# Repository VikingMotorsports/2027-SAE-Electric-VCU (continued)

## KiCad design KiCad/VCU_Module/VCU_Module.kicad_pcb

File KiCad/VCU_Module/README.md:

---
title: "**Viking MotorSports VCU Module**"
subtitle: |
  **Fabrication and Assembly Information**\
  For build TIME-STAMP
fontsize: 10pt
geometry:
  - margin=0.5in
toc: true
toc-depth: 2
colorlinks: true
urlcolor: blue
---

\newpage

# About this Board

## Board Description

*Describe board here*

## Documentation Links

*Link to documentation here*

## Documentation Files

| Filename                        | Notes                                    |
| ------------------------------- | ---------------------------------------- |
| README.pdf                      | This README file                         |
| PROJECT-NAME-outline.dxf        | Board outline (with holes) in DXF format |
| PROJECT-NAME-pcba.step          | 3D model of PCBA (with components)       |
| PROJECT-NAME-render-bot.jpg     | Render of the top of the 3D model        |
| PROJECT-NAME-render-bot.jpg     | Render of the bottom of the 3D model     |
| PROJECT-NAME-schematic.pdf      | PDF of board schematics                  |

## Contact Information

- Website: *website*
- Email: *email*

## Board Renders

{width=50%}
{width=50%}

\newpage

# Printed Circuit Board (PCB) Fabrication Information

## Board Info

- 2 layer board
- Bounding box is *TBD*
- Board thickness is 1.59 mm (0.063 inch)

## Board Requirements

- Design Rules
    - Minimum Trace / Space design rulea: 0.1524 mm (6.0 mil) / 0.1524 mm (6.0 mil)
    - Outer dimension router tolerance: +/- 0.254 mm (10.0 mil)
    - Hole placement tolerance: +/- 0.075 mm (3.0 mil)
- Drills
   - Drill Positional Tolerance: 0.051 mm (2.0 mil)
   - Drill Size tolerance: +/- 0.064 mm (2.5 mil)
- Plated/Un-plated holes
  - There are no un-plated (NPT) holes
  - There are 96 plated through (PTH) holes
  - PTH minimum diameter: 0.254 mm (10 mil)
  - PTH minimum annulus: 0.102 mm (4 mil) radius
- Outline/Routing
  - No requirements.
- Slots
  - There are no slots.
- Cutouts
  - There are no cutouts
- There are 3 fiducials on the top layer.
- Panel tabs ("mouse bites")
   - Card edges must be smooth; no mouse bites or other intrusions into the card outline.
   - If external mouse bites are required, minimize and customer will remove by hand before assembly.
- If not otherwise specified, build to IPC 6012 Class 2 or better.

## Materials

- No requirements for materials.
- Copper Surface treatment should be ENIG, althogh immersion Silver is acceptable.
- White silkscreen on top and bottom surface
- Taiyo PSR-4000 or equivalent soldermask on top and bottom, no requirements for color.

## Stack Up

- Any FR4 like material is acceptable.
- 1 oz Copper on top and bottom layers
- 1.6 mm thick when done (1/16 inch)

## Array / Panel Information

- Coordinate with Contract Manufacturer (CM) for optimal size of this panel.
- If no feedback from CM, then produce single boards (no panel).

## Fabrication Files

### IPC-2581 File

| Filename                 | Notes                                   |
| ------------------------ | --------------------------------------- |
| PROJECT-NAME-ipc2581.xml | IPC-2581 board information file         |

### Legacy PCB Files

| Filename                      | Notes                                         |
| ------------------------------| --------------------------------------------- |
| PROJECT-NAME-Edge_Cuts.gbr    | RS274X file for the dimension (outline) layer |
| PROJECT-NAME-F_Silkscreen.gbr | RS274X file for the top silkscreen            |
| PROJECT-NAME-F_Mask.gbr       | RS274X file for the top soldermask            |
| PROJECT-NAME-F_Cu.gbr         | RS274X file for the top copper layer          |
| PROJECT-NAME-In1_Cu.gbr       | RS274X file for the layer 2 copper            |
| PROJECT-NAME-In2_Cu.gbr       | RS274X file for the layer 3 copper            |
| PROJECT-NAME-B_Cu.gbr         | RS274X file for the bottom copper layer       |
| PROJECT-NAME-B_Mask.gbr       | RS274X file for the bottom soldermask         |
| PROJECT-NAME-B_Silkscreen.gbr | RS274X file for the bottom silkscreen         |
| PROJECT-NAME-NPTH.drl         | Excellon file for non-plated through holes    |
| PROJECT-NAME-PTH.drl          | Excellon file for plated through holes        | 

\newpage

# Printed Circuit Board Assembly (PCBA) Information

## Assembly Info

- All components are on the top side of the board.
- This PCBA has two components that are SMT components with through-hole mechanical leads.

## Assembly Requirements

- Assemble to IPC Class 2 or better
- Solder paste can be ROHS or leaded.
- No clean, or Aqueous flux and wash, can be used.
- No conformal coating.

## Component Specific Assembly Information

- None

## Assembly Files

### IPC-2581 File

| Filename                 | Notes                           |
| ------------------------ | ------------------------------- |
| PROJECT-NAME-ipc2581.xml | IPC-2581 board information file |

### Bill of Materials (BOM)

| Filename             | Description                            |
| -------------------- | -------------------------------------- |
| PROJECT-NAME-bom.csv | BOM in Comma Separated Variable format |

### Solder Paste Stencils

| Filename                 | Notes                                            |
| ------------------------ | ------------------------------------------------ |
| PROJECT-NAME-B_Paste.gbr | RS274X file for top/front solder paste stencil   |
| PROJECT-NAME-F_Paste.gbr | RS274X file for bottom/back solder paste stencil |

### Mounting/Placement Location

| Filename            | Description                                 |
| ------------------- | ------------------------------------------- |
| PROJECT-NAME-3u.pos | Pick and place locations for components     |

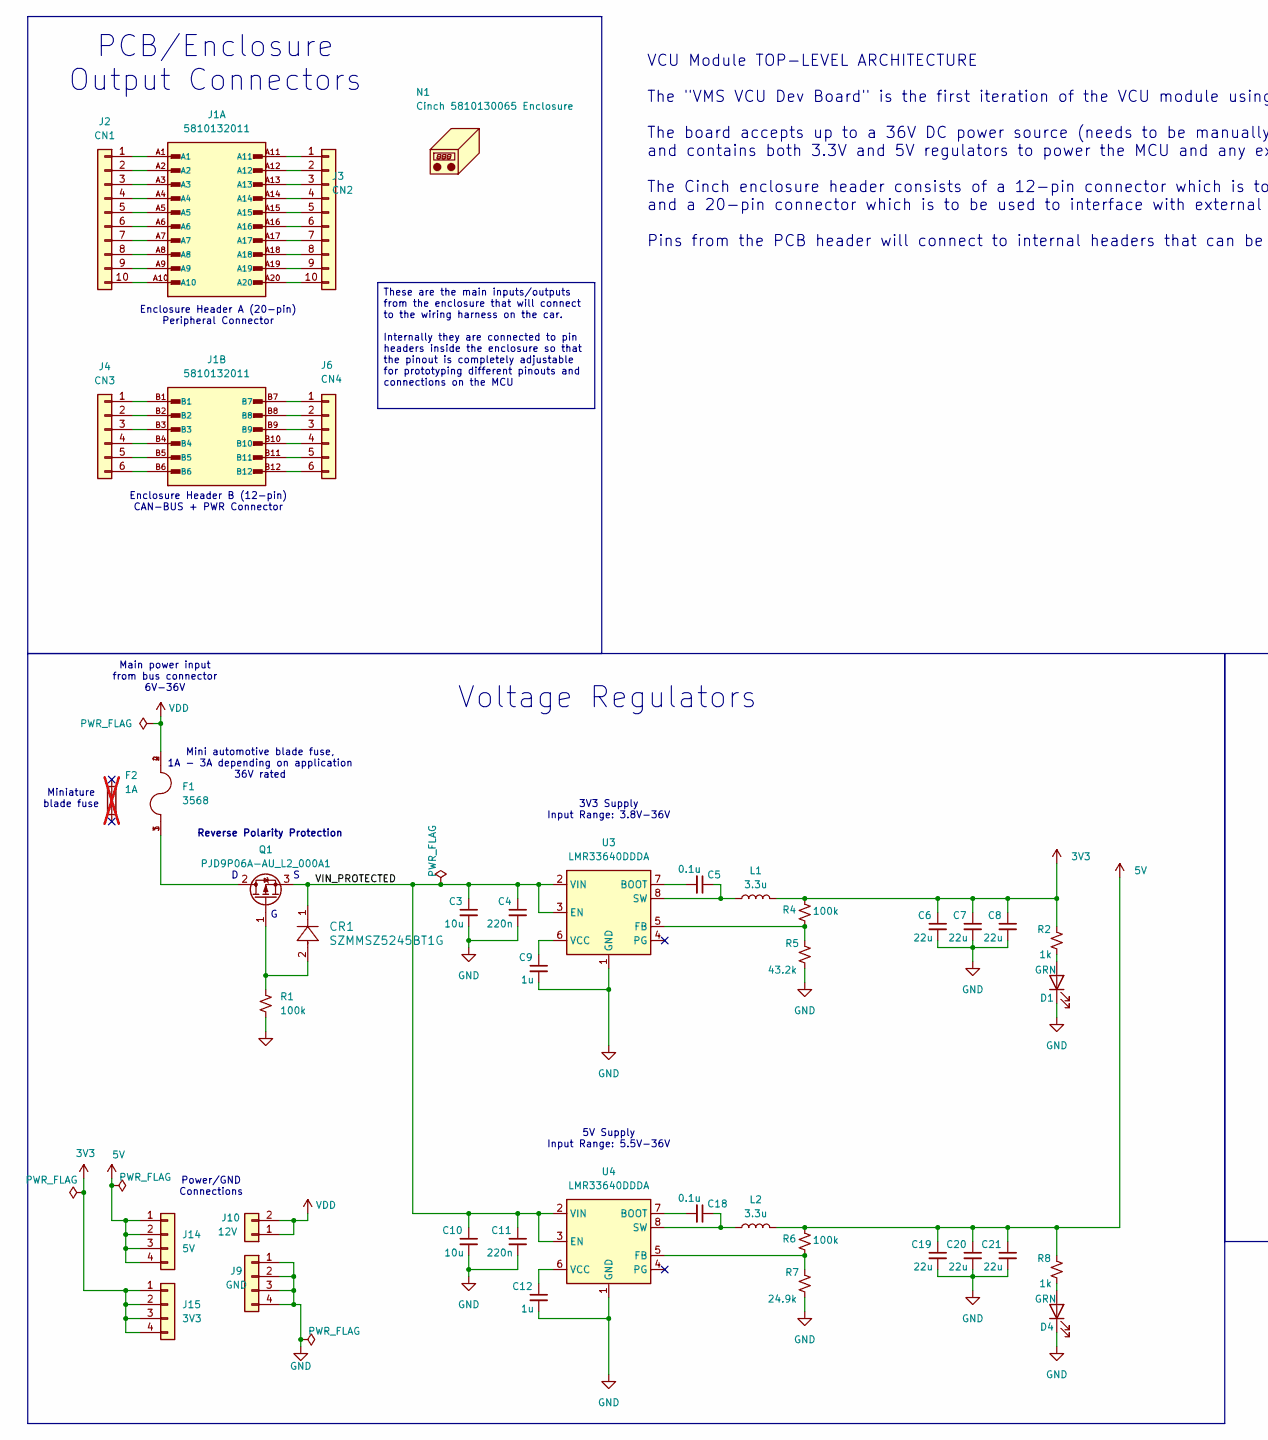
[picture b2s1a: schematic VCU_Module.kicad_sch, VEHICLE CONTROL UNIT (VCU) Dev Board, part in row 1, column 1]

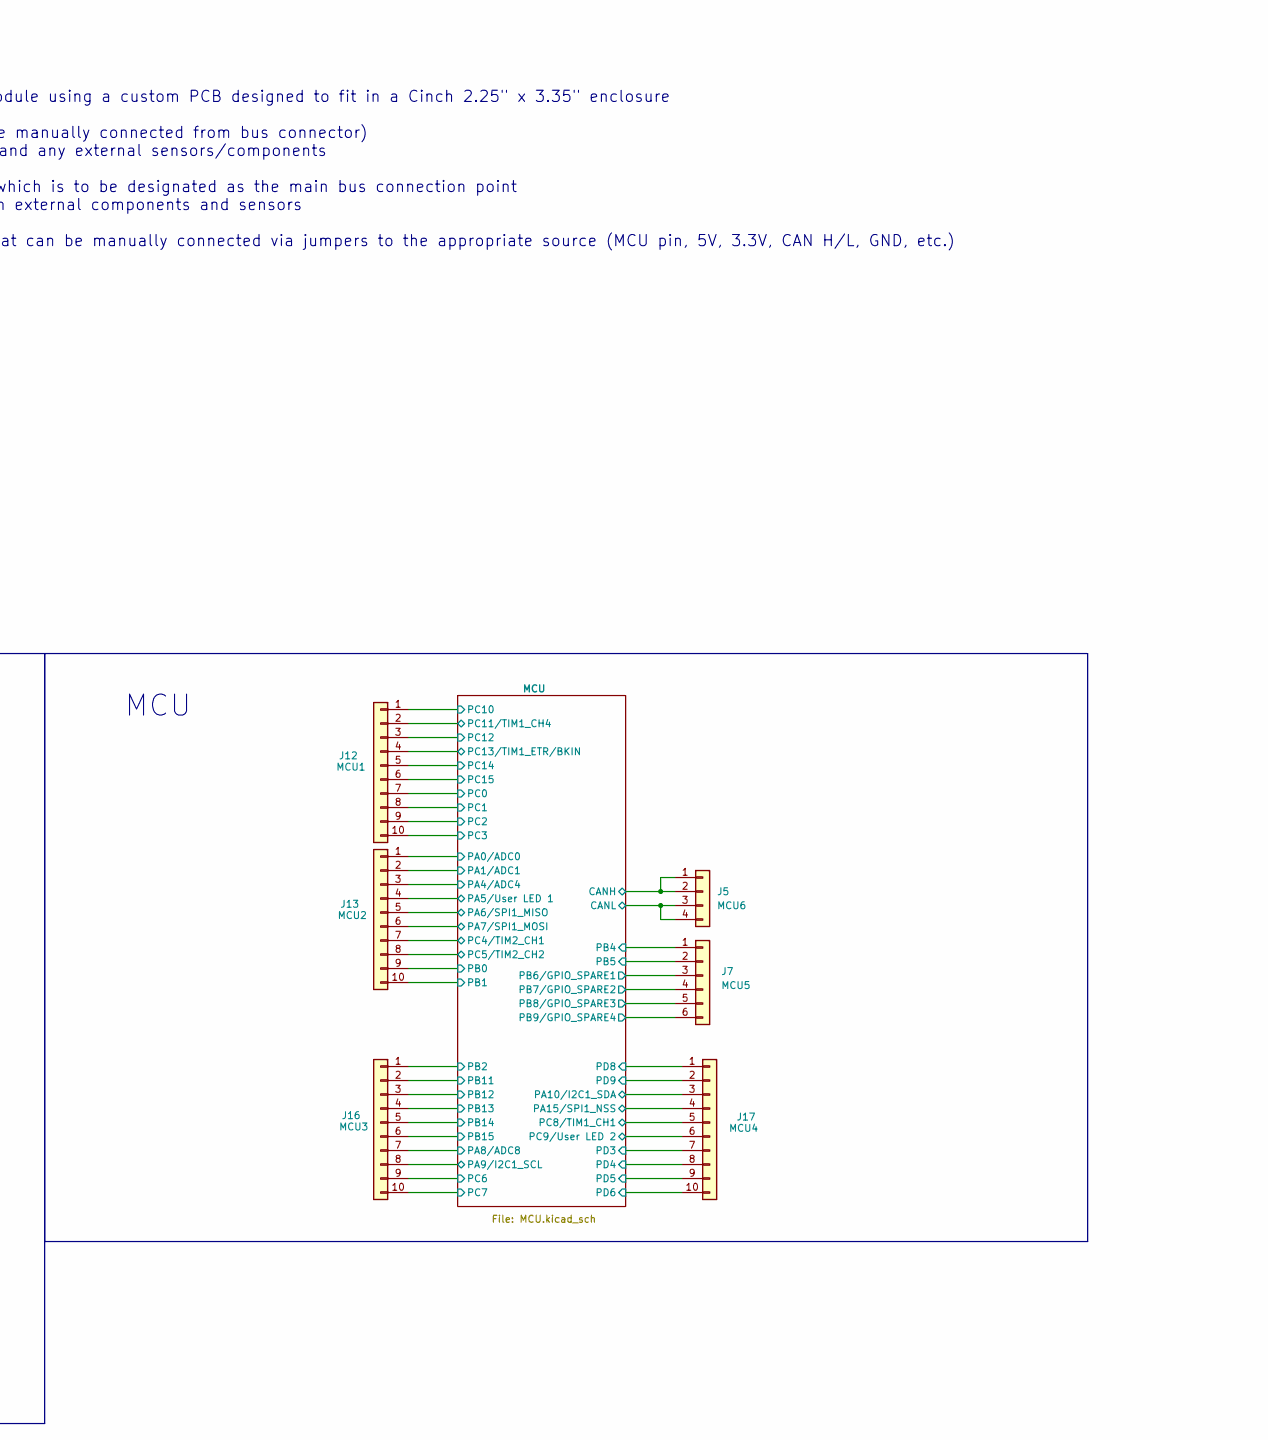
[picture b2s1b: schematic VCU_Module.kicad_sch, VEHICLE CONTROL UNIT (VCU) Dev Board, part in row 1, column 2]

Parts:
C3, C10: 10u; C_0805_2012Metric; MPN GRT21BR61H475KE13L
C4, C11: 220n; C_0805_2012Metric; MPN CL21B224KBFVPNE
C5, C18: 0.1u; C_0805_2012Metric; MPN GCJ21BR72A104KA01L
C6, C7, C8, C19, C20, C21: 22u; C_0805_2012Metric; MPN GRT21BR61C226ME13K
C9, C12: 1u; C_0805_2012Metric; MPN CGA4J3X7S2A105K125AB
CR1: SZMMSZ5245BT1G; SOD123_DIO; MPN SZMMSZ5245BT1G
D1, D4: GRN; LED_0805_2012Metric_Pad1.15x1.40mm_HandSolder; MPN SMLMN2ECTT86C
F1: 3568; FUSE_3568; PARTREV C
F2: 1A; not fitted
J1: 5810132011; Cinch_5810132011_PCB_Header; PARTREV B
J2: CN1; 1x10_Header_f; MPN PPPC101LFBN-RC
J3: CN2; 1x10_Header_f; MPN PPPC101LFBN-RC
J4: CN3; PinHeader_1x06_P2.54mm_Vertical; MPN PPPC061LFBN-RC
J5: MCU6; PinHeader_1x04_P2.54mm_Vertical; MPN PPPC041LFBN-RC
J6: CN4; PinHeader_1x06_P2.54mm_Vertical; MPN PPPC061LFBN-RC
J7: MCU5; PinHeader_1x06_P2.54mm_Vertical; MPN PPPC061LFBN-RC
J9: GND; PinHeader_1x04_P2.54mm_Vertical; MPN PPPC041LFBN-RC
J10: 12V; PinHeader_1x02_P2.54mm_Vertical; MPN PPPC021LFBN-RC
J12: MCU1; 1x10_Header_f; MPN PPPC101LFBN-RC
J13: MCU2; 1x10_Header_f; MPN PPPC101LFBN-RC
J14: 5V; PinHeader_1x04_P2.54mm_Vertical; MPN PPPC041LFBN-RC
J15: 3V3; PinHeader_1x04_P2.54mm_Vertical; MPN PPPC041LFBN-RC
J16: MCU3; 1x10_Header_f; MPN PPPC101LFBN-RC
J17: MCU4; 1x10_Header_f; MPN PPPC101LFBN-RC
L1, L2: 3.3u; L_0805_2012Metric_Pad1.05x1.20mm_HandSolder; MPN AKPB002012103R3MA2
N1: Cinch 5810130065 Enclosure; N/A; MPN 5810130065
Q1: PJD9P06A-AU_L2_000A1; TO-252-2; MPN PJD9P06A-AU_L2_000A1
R1, R4, R6: 100k; R_0805_2012Metric; MPN SG73S2ATTD1003F
R2, R8: 1k; R_0805_2012Metric; MPN SG73S2ATTD1001F
R5: 43.2k; R_0805_2012Metric; MPN RK73H2ATTD4322F
R7: 24.9k; R_0805_2012Metric; MPN RK73H2ATTD2492F
U3, U4: LMR33640DDDA; Texas_HSOP-8-1EP_3.9x4.9mm_P1.27mm_ThermalVias; MPN LMR33640DDDAR

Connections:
3V3: C6.1, C7.1, C8.1, J15.1, J15.2, J15.3, J15.4, L1.2, R2.2, R4.2; also elsewhere on the board
5V: C19.1, C20.1, C21.1, J14.1, J14.2, J14.3, J14.4, L2.2, R6.2, R8.2; also elsewhere on the board
/MCU/CANH: J5.1, J5.2; also elsewhere on the board
/MCU/CANL: J5.3, J5.4; also elsewhere on the board
/MCU/PA0/ADC0: J13.1; also elsewhere on the board
/MCU/PA1/ADC1: J13.2; also elsewhere on the board
/MCU/PA4/ADC4: J13.3; also elsewhere on the board
/MCU/PA5/User LED 1: J13.4; also elsewhere on the board
/MCU/PA6/SPI1_MISO: J13.5; also elsewhere on the board
/MCU/PA7/SPI1_MOSI: J13.6; also elsewhere on the board
/MCU/PA8/ADC8: J16.7; also elsewhere on the board
/MCU/PA9/I2C1_SCL: J16.8; also elsewhere on the board
/MCU/PA10/I2C1_SDA: J17.3; also elsewhere on the board
/MCU/PA15/SPI1_NSS: J17.4; also elsewhere on the board
/MCU/PB0: J13.9; also elsewhere on the board
/MCU/PB1: J13.10; also elsewhere on the board
/MCU/PB2: J16.1; also elsewhere on the board
/MCU/PB4: J7.1; also elsewhere on the board
/MCU/PB5: J7.2; also elsewhere on the board
/MCU/PB6/GPIO_SPARE1: J7.3; also elsewhere on the board
/MCU/PB7/GPIO_SPARE2: J7.4; also elsewhere on the board
/MCU/PB8/GPIO_SPARE3: J7.5; also elsewhere on the board
/MCU/PB9/GPIO_SPARE4: J7.6; also elsewhere on the board
/MCU/PB11: J16.2; also elsewhere on the board
/MCU/PB12: J16.3; also elsewhere on the board
/MCU/PB13: J16.4; also elsewhere on the board
/MCU/PB14: J16.5; also elsewhere on the board
/MCU/PB15: J16.6; also elsewhere on the board
/MCU/PC0: J12.7; also elsewhere on the board
/MCU/PC1: J12.8; also elsewhere on the board
/MCU/PC2: J12.9; also elsewhere on the board
/MCU/PC3: J12.10; also elsewhere on the board
/MCU/PC4/TIM2_CH1: J13.7; also elsewhere on the board
/MCU/PC5/TIM2_CH2: J13.8; also elsewhere on the board
/MCU/PC6: J16.9; also elsewhere on the board
/MCU/PC7: J16.10; also elsewhere on the board
/MCU/PC8/TIM1_CH1: J17.5; also elsewhere on the board
/MCU/PC9/User LED 2: J17.6; also elsewhere on the board
/MCU/PC10: J12.1; also elsewhere on the board
/MCU/PC11/TIM1_CH4: J12.2; also elsewhere on the board
/MCU/PC12: J12.3; also elsewhere on the board
/MCU/PC13/TIM1_ETR/BKIN: J12.4; also elsewhere on the board
/MCU/PC14: J12.5; also elsewhere on the board
/MCU/PC15: J12.6; also elsewhere on the board
/MCU/PD3: J17.7; also elsewhere on the board
/MCU/PD4: J17.8; also elsewhere on the board
/MCU/PD5: J17.9; also elsewhere on the board
/MCU/PD6: J17.10; also elsewhere on the board
/MCU/PD8: J17.1; also elsewhere on the board
/MCU/PD9: J17.2; also elsewhere on the board
/VIN_PROTECTED: C3.1, C4.1, C10.1, C11.1, CR1.1, Q1.3 (S), U3.2 (VIN), U3.3 (EN), U4.2 (VIN), U4.3 (EN)
GND: C3.2, C4.2, C6.2, C7.2, C8.2, C9.2, C10.2, C11.2, C12.2, C19.2, C20.2, C21.2, D1.1 (K), D4.1 (K), J9.1, J9.2, J9.3, J9.4, R1.2, R5.1, R7.1, U3.1 (GND), U3.9 (GND), U4.1 (GND), U4.9 (GND); also elsewhere on the board
unnamed: D1.2 (A), R2.1
unnamed: D4.2 (A), R8.1
unnamed: J1.A1, J2.1
unnamed: J1.A2, J2.2
unnamed: J1.A3, J2.3
unnamed: J1.A4, J2.4
unnamed: J1.A5, J2.5
unnamed: J1.A6, J2.6
unnamed: J1.A7, J2.7
unnamed: J1.A8, J2.8
unnamed: J1.A9, J2.9
unnamed: J1.A10, J2.10
unnamed: J1.A11, J3.1
unnamed: J1.A12, J3.2
unnamed: J1.A13, J3.3
unnamed: J1.A14, J3.4
unnamed: J1.A15, J3.5
unnamed: J1.A16, J3.6
unnamed: J1.A17, J3.7
unnamed: J1.A18, J3.8
unnamed: J1.A19, J3.9
unnamed: J1.A20, J3.10
unnamed: J1.B1, J4.1
unnamed: J1.B2, J4.2
unnamed: J1.B3, J4.3
unnamed: J1.B4, J4.4
unnamed: J1.B5, J4.5
unnamed: J1.B6, J4.6
unnamed: J1.B7, J6.1
unnamed: J1.B8, J6.2
unnamed: J1.B9, J6.3
unnamed: J1.B10, J6.4
unnamed: J1.B11, J6.5
unnamed: J1.B12, J6.6
unnamed: F1.1, F1.3, Q1.2 (D)
unnamed: CR1.2, Q1.1 (G), R1.1
unnamed: C5.2, U3.7 (BOOT)
unnamed: R4.1, R5.2, U3.5 (FB)
unnamed: C5.1, L1.1, U3.8 (SW)
unnamed: C9.1, U3.6 (VCC)
unnamed: C18.2, U4.7 (BOOT)
unnamed: R6.1, R7.2, U4.5 (FB)
unnamed: C18.1, L2.1, U4.8 (SW)
unnamed: C12.1, U4.6 (VCC)
VDD: F1.2, F1.4, J10.1, J10.2

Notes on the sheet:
Reverse Polarity Protection
Enclosure Header B (12-pin) CAN-BUS + PWR Connector
5V Supply Input Range: 5.5V-36V
Main power input from bus connector 6V-36V
3V3 Supply Input Range: 3.8V-36V
PCB/Enclosure Output Connectors
MCU
Power/GND Connections
Mini automotive blade fuse, 1A - 3A depending on application 36V rated
Miniature blade fuse
VCU Module TOP-LEVEL ARCHITECTURE The "VMS VCU Dev Board" is the first iteration of the VCU module using a custom PCB designed to fit in a Cinch 2.25" x 3.35" enclosure The board accepts up to a 36V DC power source (needs to be manually connected from bus connector) and contains both 3.3V and 5V re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
Enclosure Header A (20-pin) Peripheral Connector
Voltage Regulators
These are the main inputs/outputs from the enclosure that will connect to the wiring harness on the car. Internally they are connected to pin headers inside the enclosure so that the pinout is completely adjustable for prototyping different pinouts and connections on the MCU

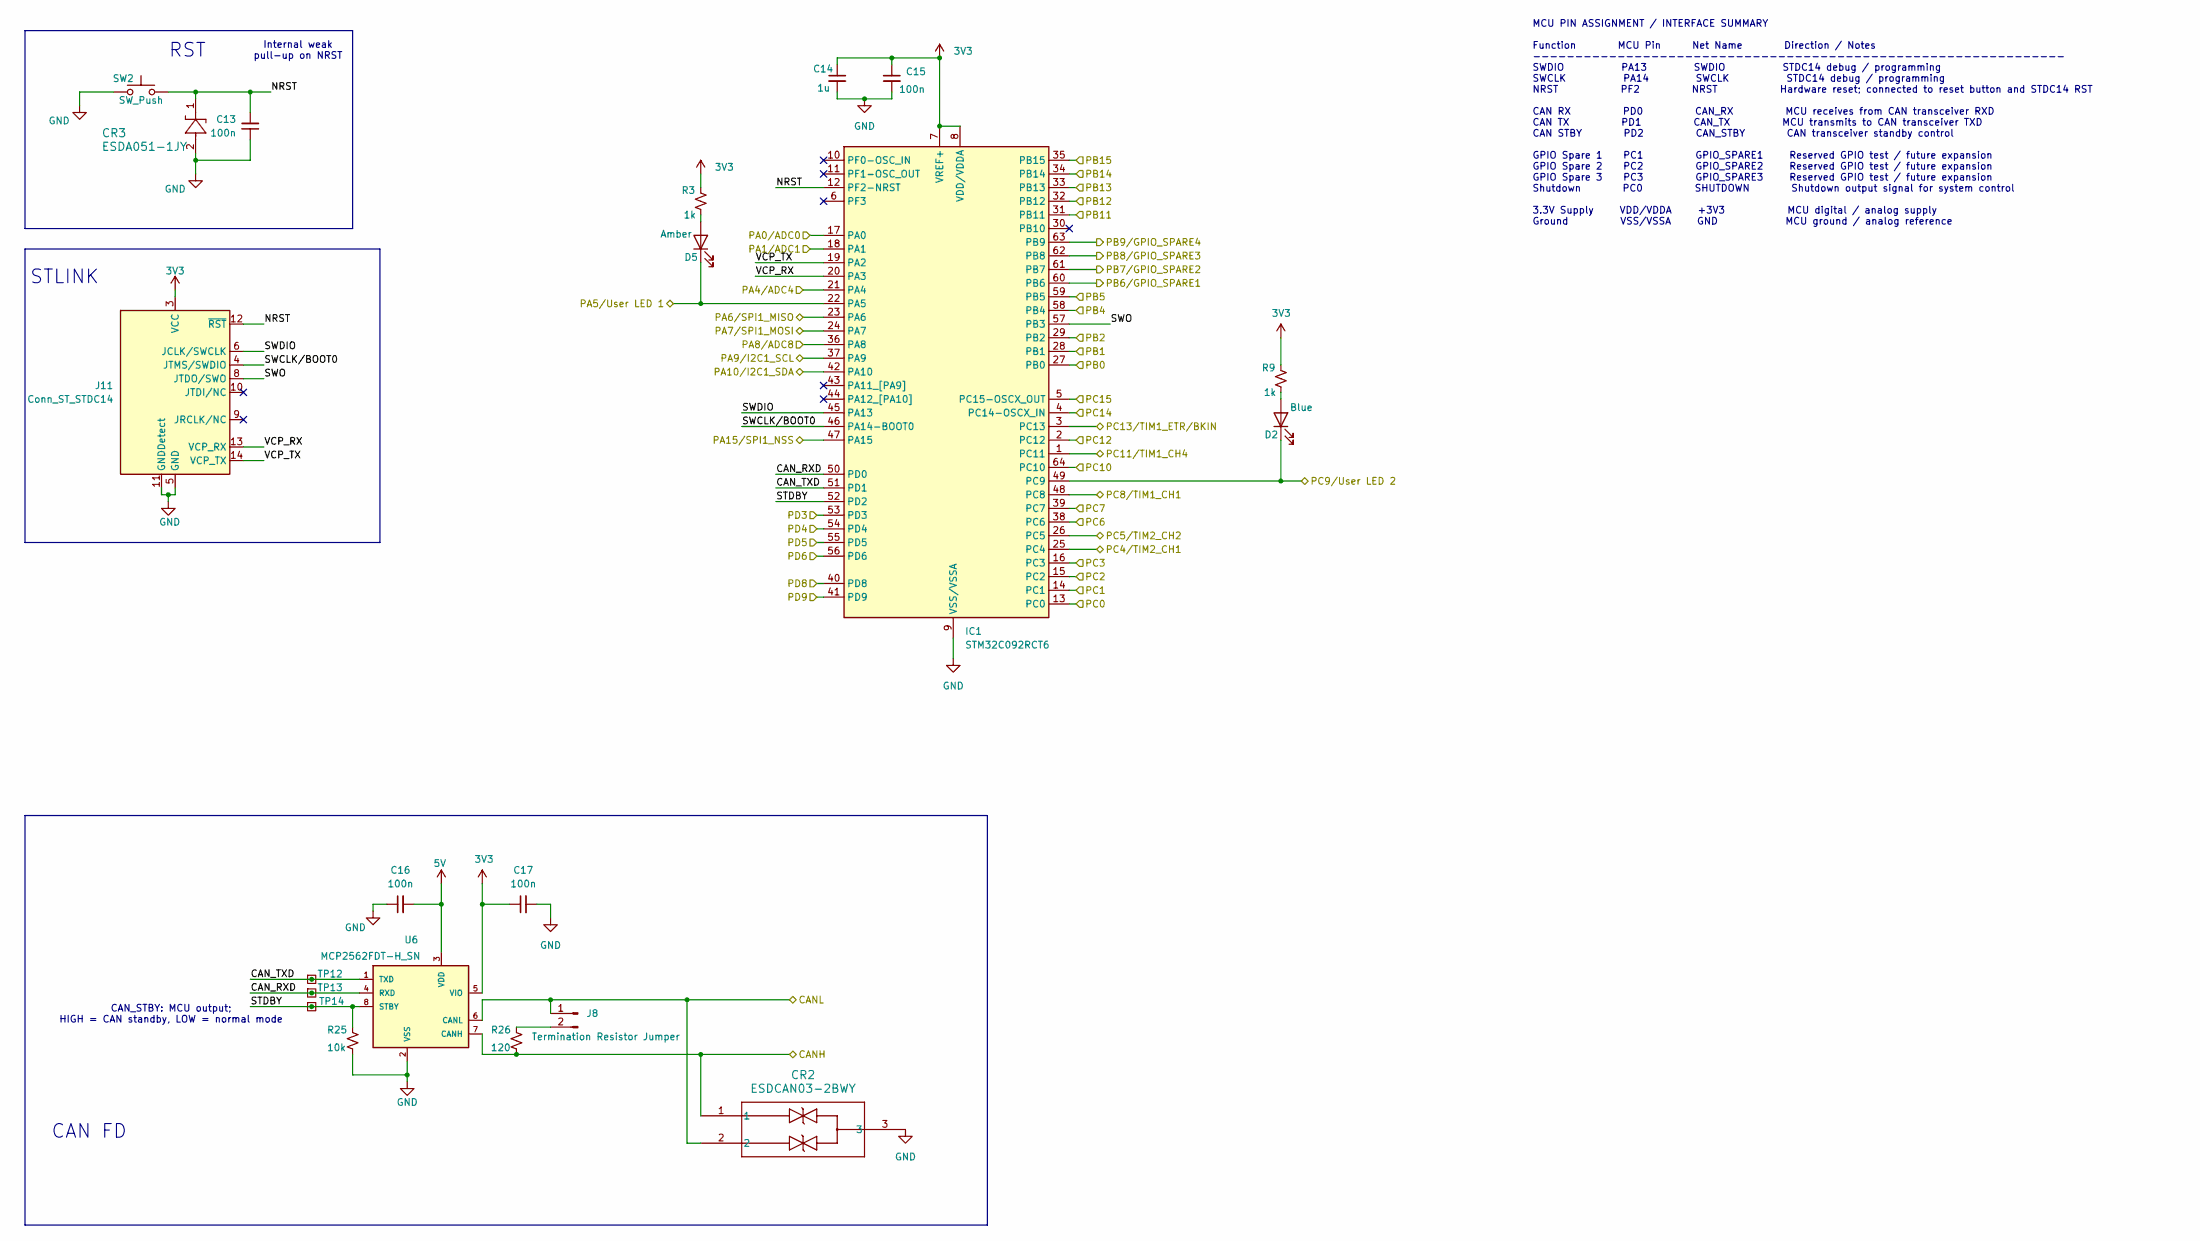
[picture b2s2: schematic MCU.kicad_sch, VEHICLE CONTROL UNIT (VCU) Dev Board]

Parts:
C13, C15, C16, C17: 100n; C_0805_2012Metric; MPN GCJ21BR72A104KA01L
C14: 1u; C_0805_2012Metric; MPN CGA4J3X7S2A105K125AB
CR2: ESDCAN03-2BWY; SOT323-3L_STM; MPN ESDCAN03-2BWY
CR3: ESDA051-1JY; D_SOD-323; MPN ESDA051-1JY
D2: Blue; LED_0805_2012Metric_Pad1.15x1.40mm_HandSolder; MPN SMLMN2BCTT86C
D5: Amber; LED_0805_2012Metric_Pad1.15x1.40mm_HandSolder; MPN SML-H12D8TT86C
IC1: STM32C092RCT6; QFP50P1200X1200X160-64N; Manufacturer_Part_Number STM32C092RCT6; Mouser Part Number 511-STM32C092RCT6
J8: Termination Resistor Jumper; PinHeader_1x02_P2.54mm_Vertical; MPN TS-102-T-A
J11: Conn_ST_STDC14; PinHeader_2x07_P1.27mm_Vertical; MPN FTSH-107-01-F-DV-K
R3, R9: 1k; R_0805_2012Metric; MPN SG73S2ATTD1001F
R25: 10k; R_0805_2012Metric; MPN SG73S2ATTD103J
R26: 120; R_0805_2012Metric; MPN SG73S2ATTD1200F
SW2: SW_Push; SW_PUSH_6mm_H4.3mm; MPN B3F-1000
TP12, TP13, TP14: TestPoint_Small; TestPoint_THTPad_D1.5mm_Drill0.7mm
U6: MCP2562FDT-H_SN; SOIC127P600X175-8N; MPN MCP2562FDT-H/SN

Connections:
3V3: C14.1, C15.1, C17.1, IC1.7 (VREF+), IC1.8 (VDD/VDDA), J11.3 (VCC), R3.2, R9.2, U6.5 (VIO); also elsewhere on the board
5V: C16.2, U6.3 (VDD); also elsewhere on the board
/MCU/CANH: CR2.1, R26.2, U6.7 (CANH); also elsewhere on the board
/MCU/CANL: CR2.2, J8.1, U6.6 (CANL); also elsewhere on the board
/MCU/CAN_RXD: IC1.50 (PD0), TP13.1 (1_1), U6.4 (RXD)
/MCU/CAN_TXD: IC1.51 (PD1), TP12.1 (1_1), U6.1 (TXD)
/MCU/NRST: C13.2, CR3.1, IC1.12 (PF2-NRST), J11.12 (~RST), SW2.1
/MCU/PA0/ADC0: IC1.17 (PA0); also elsewhere on the board
/MCU/PA1/ADC1: IC1.18 (PA1); also elsewhere on the board
/MCU/PA4/ADC4: IC1.21 (PA4); also elsewhere on the board
/MCU/PA5/User LED 1: D5.1 (K), IC1.22 (PA5); also elsewhere on the board
/MCU/PA6/SPI1_MISO: IC1.23 (PA6); also elsewhere on the board
/MCU/PA7/SPI1_MOSI: IC1.24 (PA7); also elsewhere on the board
/MCU/PA8/ADC8: IC1.36 (PA8); also elsewhere on the board
/MCU/PA9/I2C1_SCL: IC1.37 (PA9); also elsewhere on the board
/MCU/PA10/I2C1_SDA: IC1.42 (PA10); also elsewhere on the board
/MCU/PA15/SPI1_NSS: IC1.47 (PA15); also elsewhere on the board
/MCU/PB0: IC1.27 (PB0); also elsewhere on the board
/MCU/PB1: IC1.28 (PB1); also elsewhere on the board
/MCU/PB2: IC1.29 (PB2); also elsewhere on the board
/MCU/PB4: IC1.58 (PB4); also elsewhere on the board
/MCU/PB5: IC1.59 (PB5); also elsewhere on the board
/MCU/PB6/GPIO_SPARE1: IC1.60 (PB6); also elsewhere on the board
/MCU/PB7/GPIO_SPARE2: IC1.61 (PB7); also elsewhere on the board
/MCU/PB8/GPIO_SPARE3: IC1.62 (PB8); also elsewhere on the board
/MCU/PB9/GPIO_SPARE4: IC1.63 (PB9); also elsewhere on the board
/MCU/PB11: IC1.31 (PB11); also elsewhere on the board
/MCU/PB12: IC1.32 (PB12); also elsewhere on the board
/MCU/PB13: IC1.33 (PB13); also elsewhere on the board
/MCU/PB14: IC1.34 (PB14); also elsewhere on the board
/MCU/PB15: IC1.35 (PB15); also elsewhere on the board
/MCU/PC0: IC1.13 (PC0); also elsewhere on the board
/MCU/PC1: IC1.14 (PC1); also elsewhere on the board
/MCU/PC2: IC1.15 (PC2); also elsewhere on the board
/MCU/PC3: IC1.16 (PC3); also elsewhere on the board
/MCU/PC4/TIM2_CH1: IC1.25 (PC4); also elsewhere on the board
/MCU/PC5/TIM2_CH2: IC1.26 (PC5); also elsewhere on the board
/MCU/PC6: IC1.38 (PC6); also elsewhere on the board
/MCU/PC7: IC1.39 (PC7); also elsewhere on the board
/MCU/PC8/TIM1_CH1: IC1.48 (PC8); also elsewhere on the board
/MCU/PC9/User LED 2: D2.1 (K), IC1.49 (PC9); also elsewhere on the board
/MCU/PC10: IC1.64 (PC10); also elsewhere on the board
/MCU/PC11/TIM1_CH4: IC1.1 (PC11); also elsewhere on the board
/MCU/PC12: IC1.2 (PC12); also elsewhere on the board
/MCU/PC13/TIM1_ETR/BKIN: IC1.3 (PC13); also elsewhere on the board
/MCU/PC14: IC1.4 (PC14-OSCX_IN); also elsewhere on the board
/MCU/PC15: IC1.5 (PC15-OSCX_OUT); also elsewhere on the board
/MCU/PD3: IC1.53 (PD3); also elsewhere on the board
/MCU/PD4: IC1.54 (PD4); also elsewhere on the board
/MCU/PD5: IC1.55 (PD5); also elsewhere on the board
/MCU/PD6: IC1.56 (PD6); also elsewhere on the board
/MCU/PD8: IC1.40 (PD8); also elsewhere on the board
/MCU/PD9: IC1.41 (PD9); also elsewhere on the board
/MCU/STDBY: IC1.52 (PD2), R25.1, TP14.1 (1_1), U6.8 (STBY)
/MCU/SWCLK/BOOT0: IC1.46 (PA14-BOOT0), J11.4 (JTMS/SWDIO)
/MCU/SWDIO: IC1.45 (PA13), J11.6 (JCLK/SWCLK)
/MCU/SWO: IC1.57 (PB3), J11.8 (JTDO/SWO)
/MCU/VCP_RX: IC1.20 (PA3), J11.13 (VCP_RX)
/MCU/VCP_TX: IC1.19 (PA2), J11.14 (VCP_TX)
GND: C13.1, C14.2, C15.2, C16.1, C17.2, CR2.3, CR3.2, IC1.9 (VSS/VSSA), J11.5 (GND), J11.7 (GND), J11.11 (GNDDetect), R25.2, SW2.2, U6.2 (VSS); also elsewhere on the board
unnamed: D2.2 (A), R9.1
unnamed: D5.2 (A), R3.1
unnamed: J8.2, R26.1

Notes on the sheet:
MCU PIN ASSIGNMENT / INTERFACE SUMMARY Function MCU Pin Net Name Direction / Notes --------------------------------------------------------------- SWDIO PA13 SWDIO STDC14 debug / programming SWCLK PA14 SWCLK STDC14 debug / programming NRST PF2 NRST Hardware reset; connected to reset button and STDC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
STLINK
CAN FD
RST
CAN_STBY: MCU output; HIGH = CAN standby, LOW = normal mode
Internal weak pull-up on NRST

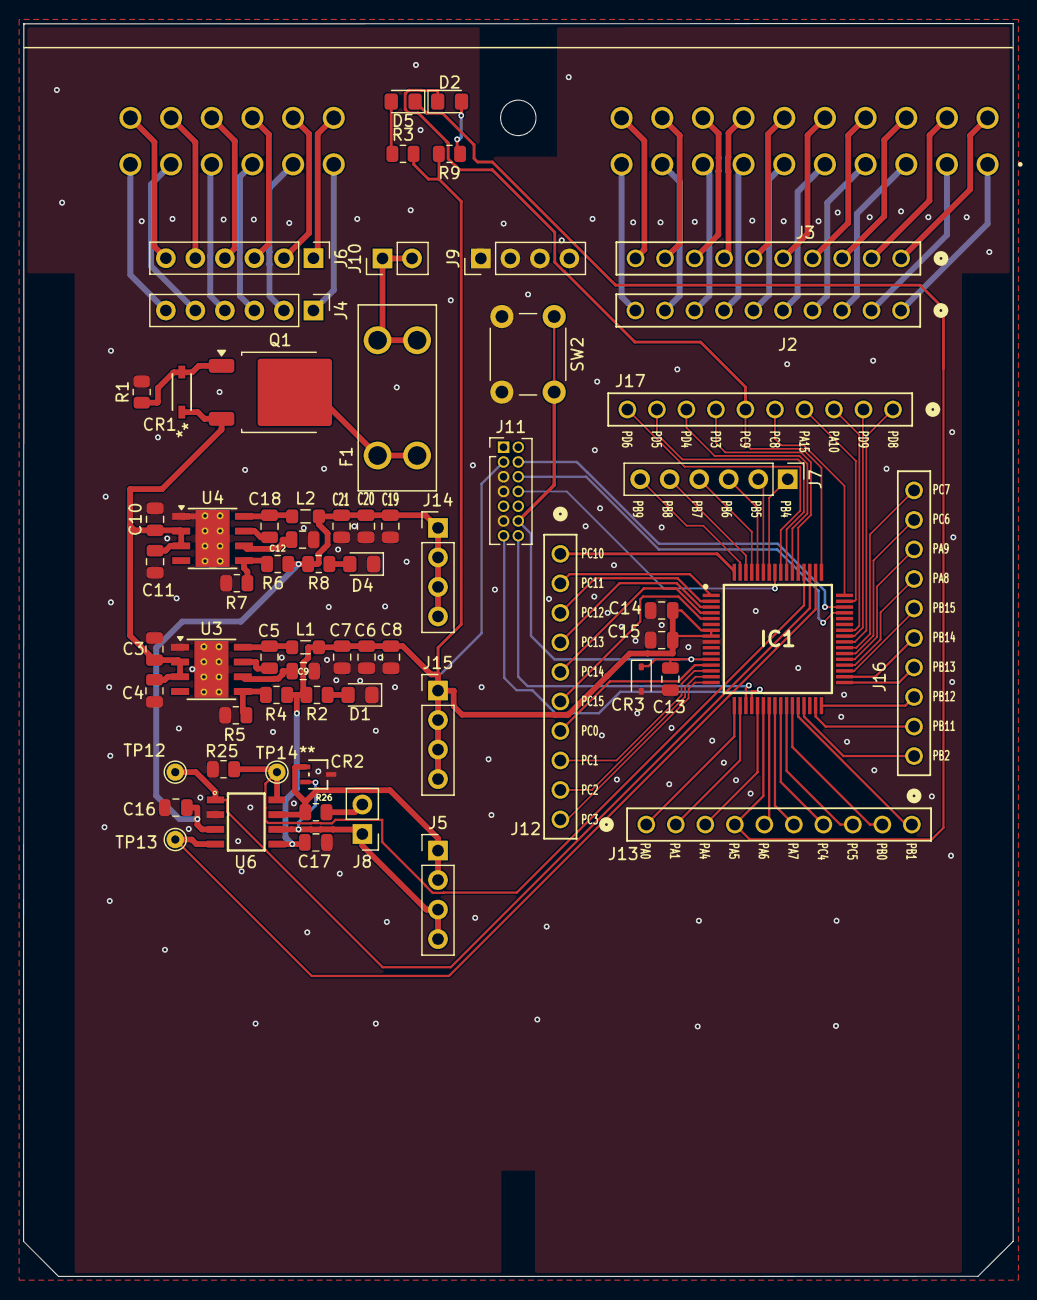
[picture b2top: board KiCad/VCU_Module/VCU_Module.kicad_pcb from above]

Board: 2 copper layers, 85.2 x 107.8 mm, 66 parts (0 on the bottom side), 109 nets.

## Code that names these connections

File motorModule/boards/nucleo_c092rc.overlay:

/*
 * Overlay for nucleo_c092rc:
 *  A0  -> PA0  -> ADC1 channel 0  (accelerator potentiometer)
 *	A1  -> PA1  -> ADC1 channel 1  (brake potentiometer)
 *  
 *	D7  -> PA8  -> TIM1_CH1 		(PWM1)
 *  D6	-> PC8	-> B
 *	D5	-> PB4	-> A
 *	
 *	D8  -> PA9  -> TIM1_CH2        (PWM2)
 *	D9	-> PB3	-> a
 *	D10	-> PA15	-> b
 */

/ {
    zephyr,user {
        io-channels = 	<&adc1 0>, <&adc1 1>;

        pwms =
			<&pwm1 1 PWM_USEC(50) PWM_POLARITY_NORMAL>,
			<&pwm1 2 PWM_USEC(50) PWM_POLARITY_NORMAL>;

		in1-gpios = <&gpiob 4 GPIO_ACTIVE_HIGH>;
		in2-gpios = <&gpioc 8 GPIO_ACTIVE_HIGH>;
		in3-gpios = <&gpiob 3 GPIO_ACTIVE_HIGH>;
		in4-gpios = <&gpioa 15 GPIO_ACTIVE_HIGH>;
    };
};

&adc1 {
	#address-cells = <1>;
	#size-cells = <0>;
	status = "okay";

	channel@0 {
		reg = <0>;
		zephyr,gain = "ADC_GAIN_1";
		zephyr,reference = "ADC_REF_INTERNAL";
		zephyr,acquisition-time = <ADC_ACQ_TIME_DEFAULT>;
		zephyr,resolution = <12>;
	};

	channel@1 {
		reg = <1>;
		zephyr,gain = "ADC_GAIN_1";
		zephyr,reference = "ADC_REF_INTERNAL";
		zephyr,acquisition-time = <ADC_ACQ_TIME_DEFAULT>;
		zephyr,resolution = <12>;
	};
};

/*
 * TIM1:
 *   CH1 -> PA8  (D7)
 *   CH2 -> PA9  (D8)
 */
&timers1 {
	status = "okay";
	st,prescaler = <0>;

	pwm1: pwm {
		status = "okay";

		pinctrl-0 = <
			&tim1_ch1_pa8
			&tim1_ch2_pa9
		>;

		pinctrl-names = "default";
	};
};

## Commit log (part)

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2026-03-21 adding sample files
2026-03-21 flash script for building from repo
2026-03-23 script for finding COM port of board and conncecting to serial port through putty
2026-03-24 added adc_dt sample along with appropriate overlay for c092 board
2026-03-27 adding lightning chart gauge files
2026-03-27 CAN database editor
2026-03-27 C# Hello World
2026-03-27 created adc/can combo app
2026-03-27 Steering Wheel Code
    This is the framework for the steering wheel sensor. At the moment, it is a potentiometer-based prototype.
2026-03-27 Steering Wheel Code
    Prelim. code for steering wheel using a potentiometer as a prototype.
2026-03-30 fixed monitor script, replacing grep with findstr
2026-03-30 added code for adc input to change LED speed
2026-03-31 Simple Display Module for Driver
    This is a preliminary test for the driver display.
2026-04-03 add adcToPi
2026-04-10 Driver Display via Serial
    Driver display that takes in serial input.
2026-04-10 vcu test code
2026-04-11 editing serial line read
2026-04-11 vcu test code
    changed app name back to canToDisplay
2026-04-11 editing serial line read
    rebase damnit!
2026-04-11 taking out the trash
2026-04-11 add gitignore
2026-04-11 cleaning
2026-04-11 removing lightningchart files, saved elsewhere
2026-04-11 ;lkfdsh;hfdsa;lkh
2026-04-11 vcu test code rebase
2026-04-11 editing serial line read
    FUCK
2026-04-17 not sure what these changes are about
2026-04-17 vulcan firmware (socketCAN
2026-04-17 NEW DISPLAY CODE (pygame)
2026-04-17 slcan firmware
2026-04-17 slcan script start and venv
2026-04-18 slcan/python-can sample read code
2026-04-19 added code to set bitrate to 500k on startup
2026-04-19 added can receiver python code
2026-04-19 updated to use socketcan
2026-04-27 Claude Generated ADC to PWM (H Bridge) Code This is demo code using Claude, Will add CAN to it later. Needs to be tested, is able to be built
2026-04-27 Change Acquisition time to ticks not time for ADC Claude had it set to time, but Zephyr works mostly in ticks from what I skimmed
2026-04-27 adding CAN messages
2026-04-28 integrating CAN_RECEIVER and driver display
2026-04-28 add bitrate and samplepoint configuration
2026-04-28 socketCAN auto config + pythoncan script
2026-04-28 Add MQTT receiver
2026-04-29 updated text color
2026-04-29 updated font
2026-04-29 major changes to CAN inputs and CAN interfacing
2026-04-29 changes to CAN inputs and update_physics()
2026-04-29 integrating pedal sensor code with can code
2026-04-29 working on pedal module
2026-04-29 drvier dash integration
2026-04-30 fixed pedal module deadzone
2026-05-01 Fixed Accelorator Stall after around 50% accelerator
2026-05-01 Changes foor friday including mqtt
2026-05-01 Adding matplotlib script (pedal)
2026-05-01 Changes To driver dash for Linux Laptop
2026-05-01 Moar Changes to Dash Display for linux laptop
2026-05-11 new VCUmodule for modular code
2026-05-13 added motor duty CAN message ID
2026-05-15 Create Dashboard Pit Display
2026-05-15 added candlelight socketCAN firmware
2026-05-17 IBT-2 H-bridge with dual pwm inputs
2026-05-20 Cleaned up comments and code Added can_database.h for defining message IDs and documentation Added struct arrays for CAN filters and frames for easier addition of new messages Flashed to board and up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
2026-05-20 added Introductory Developer's Guide PDF
2026-05-22 we should add to readme
2026-05-29 added additional adc input to board overlay file for VCUmodule
2026-05-29 Added driver_dash_pyqt.py to repo
2026-05-29 Added header for PyQt Driver Display
2026-05-29 Added MQTT and CAN Config to PyQT Display
2026-06-08 updated VCUmodule to have brake and accelerator pedal, copied driver dash file to have a copy without the mqtt stuff
2026-06-08 running driver dash with no pit display
2026-06-10 adding CAN to driver dash QT
2026-06-11 updating motor controller code
2026-06-11 motor controller
2026-06-11 added data recieving from can to motor controller
2026-06-12 Adding MqTT to driver_no_display and Python services
2026-06-12 Update comments and print statements for clarity
2026-06-12 Added improved telemetry handling
2026-06-12 Added more comments and structure
    Updated comments and structure in index.html for clarity and organization.
2026-06-12 More comments and structure
    Updated comments and structure for clarity and organization.
2026-06-12 updated motor controller to handle direction and duty based on pedal inputs
2026-06-26 added kicad files
2026-06-29 wiring gpios to connector headers in schematic
